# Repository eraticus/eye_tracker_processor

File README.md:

# eye_tracker_processor
take signal and offset plus or minus 10V and gain plus or minus 10 times

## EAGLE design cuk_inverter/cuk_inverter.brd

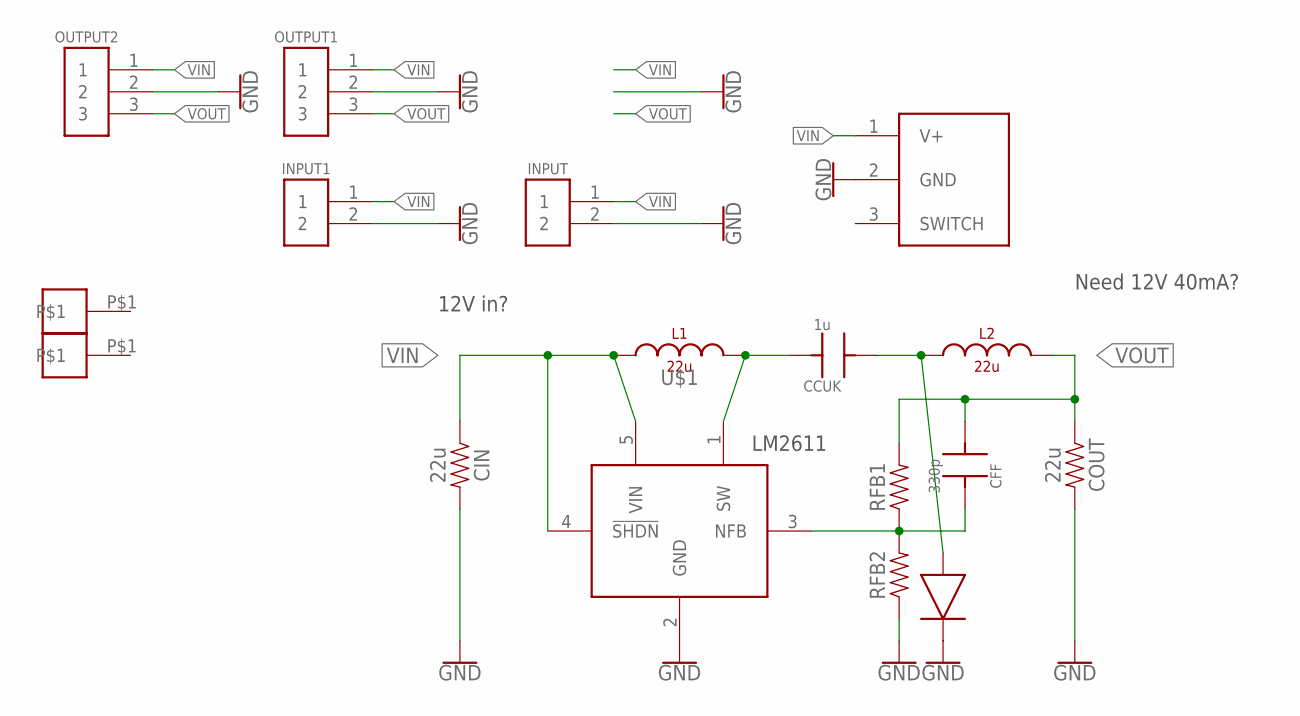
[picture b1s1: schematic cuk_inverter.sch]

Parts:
CCUK: 1u; 0805_B
CFF: 330p; 0805_B
CIN: 22u; 1206
COUT: 22u; 1206
INPUT, INPUT1: M02; OSTVN02
L1, L2: 22u; INDUCTOR_BOURNS_SRU5018
OUTPUT1, OUTPUT2: M03; OSTVN03
RFB1, RFB2: RESISTOR0805; 0805
U$1: LM2611; SOT-23
U$6, U$7: FIDUCIAL; FIDUCIAL_0.5MM
U$8: DIODE; STTH3R04U
V1: POWER_DC_BARREL_JACKCP-102A; CONN_JACK_POWER_2.1MM_PCB

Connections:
CUK: CCUK.1, L2.1, U$8.A
FB: CFF.2, RFB1.1, RFB2.2, U$1.3 (NFB)
GND: CIN.2, COUT.2, INPUT.2, INPUT1.2, OUTPUT1.2, OUTPUT2.2, RFB2.1, U$1.2 (GND), U$8.K, V1.2 (GND)
SW: CCUK.2, L1.2, U$1.1 (SW)
VIN: CIN.1, INPUT.1, INPUT1.1, L1.1, OUTPUT1.1, OUTPUT2.1, U$1.4 (!SHDN), U$1.5 (VIN), V1.1 (V+)
VOUT: CFF.1, COUT.1, L2.2, OUTPUT1.3, OUTPUT2.3, RFB1.2

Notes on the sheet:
Need 12V 40mA?
12V in?

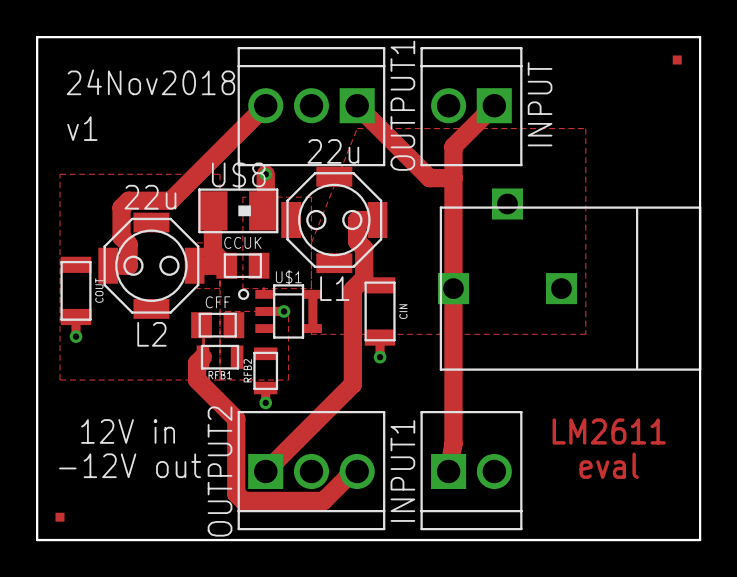
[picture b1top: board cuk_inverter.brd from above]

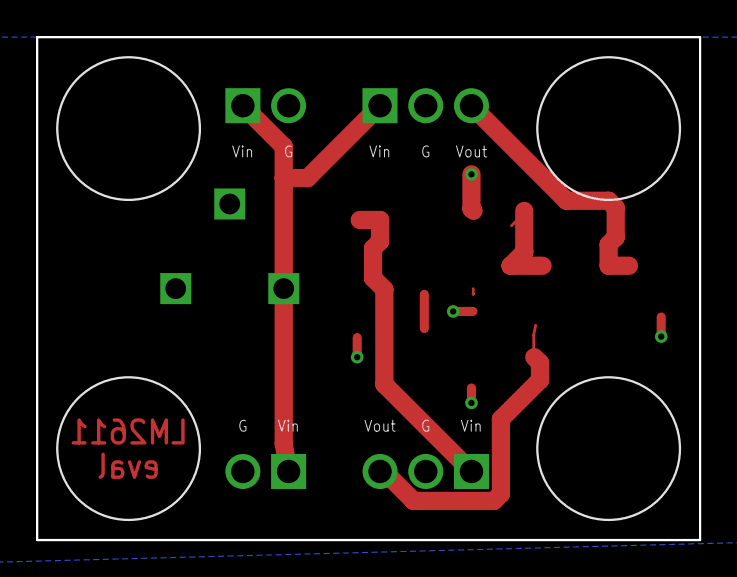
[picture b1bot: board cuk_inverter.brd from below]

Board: 2 copper layers, 36.8 x 27.9 mm, 21 parts (4 on the bottom side), 6 nets.

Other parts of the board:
U$2, U$3, U$4, U$5: SJ5302

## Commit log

2018-12-21 Adding cuk inverter test board. This design has not been breadboarded, but designed based upon datasheet.

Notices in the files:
parts and their libraries:
SparkFun-PowerSymbols: Licensing: Creative Commons ShareAlike 4.0 International - https://creativecommons.org/licenses/by-sa/4.0
